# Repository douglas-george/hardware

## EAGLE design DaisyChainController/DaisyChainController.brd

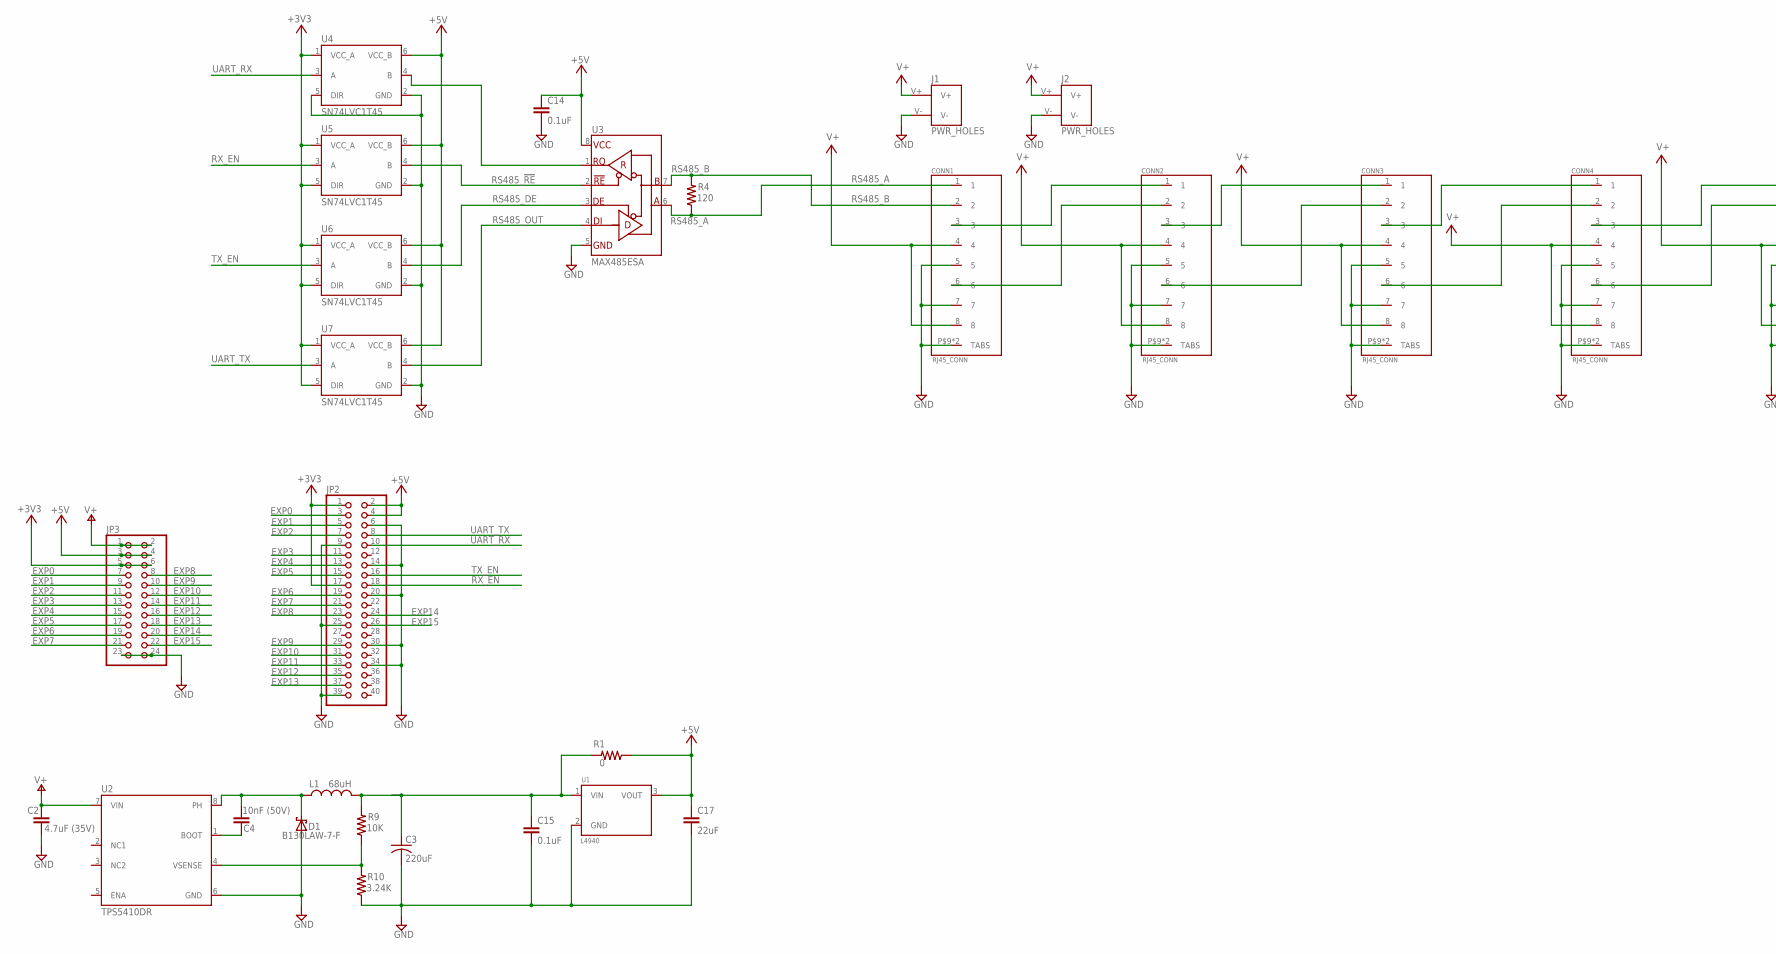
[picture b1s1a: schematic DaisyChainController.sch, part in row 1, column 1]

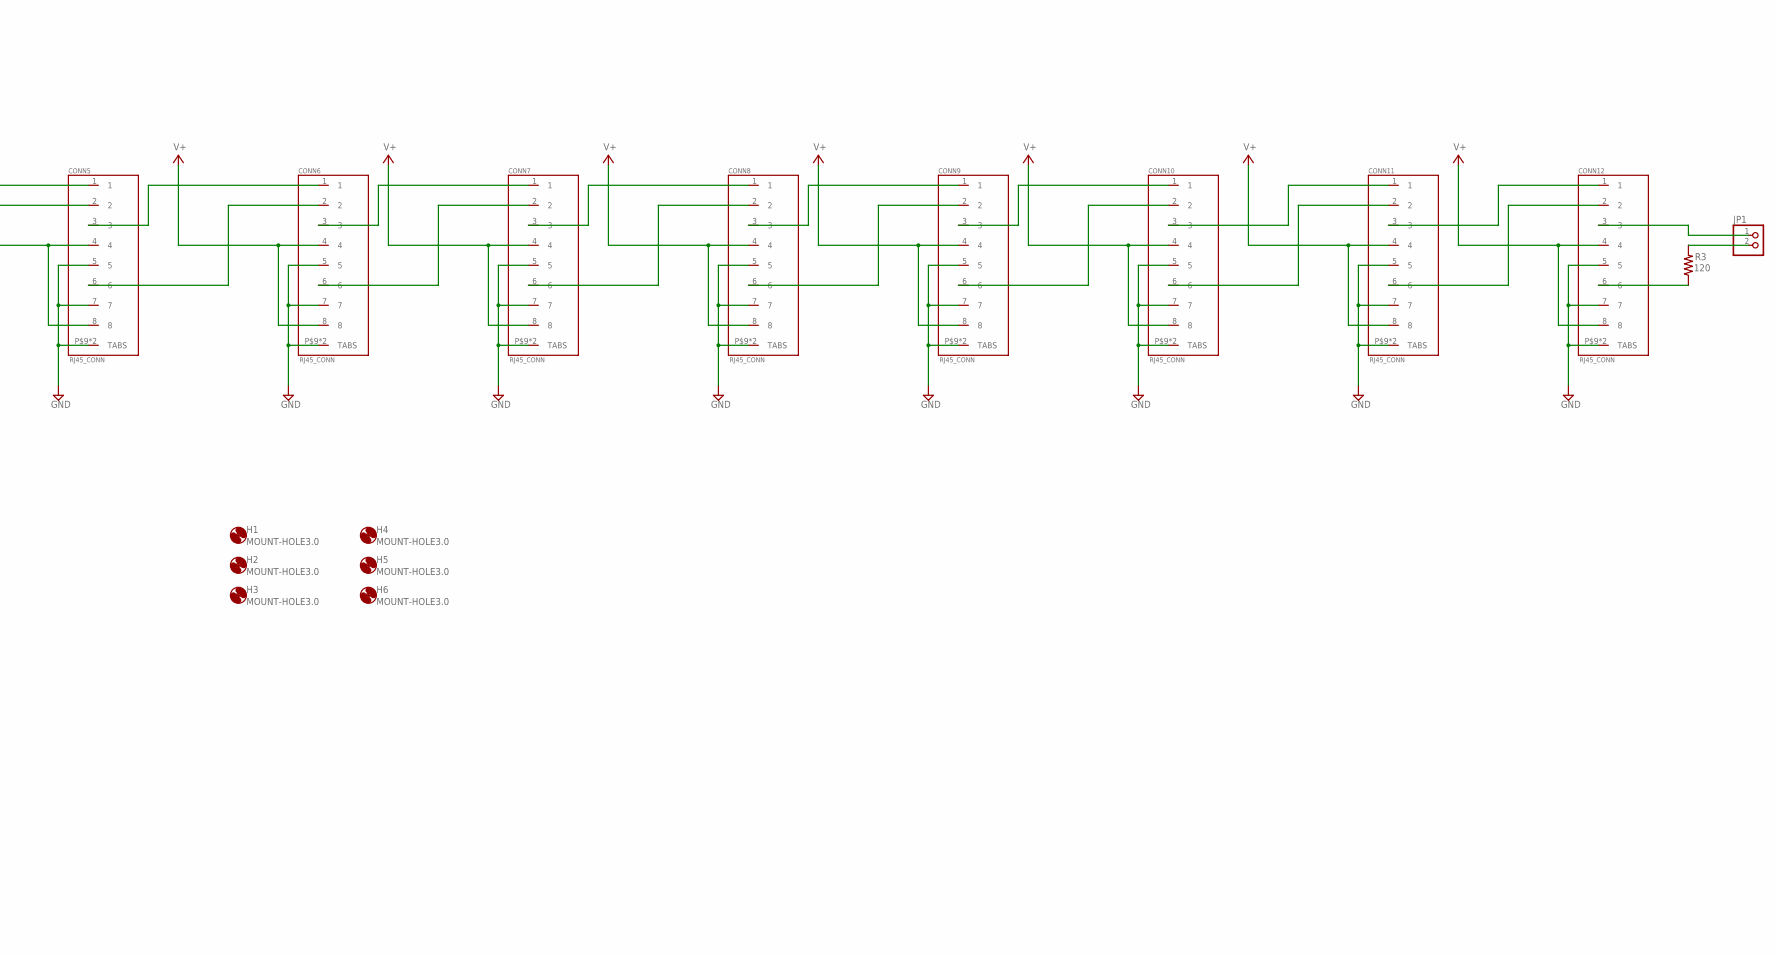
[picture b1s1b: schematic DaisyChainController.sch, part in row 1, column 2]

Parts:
C2: 4.7uF (35V); C0805
C3: 220uF; KEMET_D_CAP
C4: 10nF (50V); C0805
C14, C15: 0.1uF; C0805
C17: 22uF; C0805
CONN1, CONN2, CONN3, CONN4, CONN5, CONN6, CONN7, CONN8, CONN9, CONN10, CONN11, CONN12: RJ45_CONN; RJ45_VERT
D1: B130LAW-7-F; SOD123
H1, H2, H3, H4, H5, H6: MOUNT-HOLE3.0; 3,0
J1, J2: PWR_HOLES
JP1: PINHD-1X2; 1X02
JP2: PINHD-2X20/90; 2X20/90
JP3: PINHD-2X12; 2X12
L1: 68uH; CDRH127R
R1: 0; R0805
R3, R4: 120; R0805
R9: 10K; R0805
R10: 3.24K; R0805
U1: L4940; TO220
U2: TPS5410DR; SO08
U3: MAX485ESA; SO08
U4, U5, U6, U7: SN74LVC1T45; SOT23-6

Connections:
+3V3: JP2.1, JP2.17, JP3.5, JP3.6, U4.1 (VCC_A), U5.1 (VCC_A), U5.5 (DIR), U6.1 (VCC_A), U6.5 (DIR), U7.1 (VCC_A), U7.5 (DIR)
+5V: C14.1, C17.1, JP2.2, JP2.4, JP3.3, JP3.4, R1.1, U1.3 (VOUT), U3.8 (VCC), U4.6 (VCC_B), U5.6 (VCC_B), U6.6 (VCC_B), U7.6 (VCC_B)
EXP0: JP2.3, JP3.7
EXP1: JP2.5, JP3.9
EXP2: JP2.7, JP3.11
EXP3: JP2.11, JP3.13
EXP4: JP2.13, JP3.15
EXP5: JP2.15, JP3.17
EXP6: JP2.19, JP3.19
EXP7: JP2.21, JP3.21
EXP8: JP2.23, JP3.8
EXP9: JP2.29, JP3.10
EXP10: JP2.31, JP3.12
EXP11: JP2.33, JP3.14
EXP12: JP2.35, JP3.16
EXP13: JP2.37, JP3.18
EXP14: JP2.24, JP3.20
EXP15: JP2.26, JP3.22
GND: C2.2, C3.- (2), C14.2, C15.2, C17.2, CONN1.5, CONN1.7, CONN1.P$9 (TABS), CONN1.P$10 (TABS), CONN2.5, CONN2.7, CONN2.P$9 (TABS), CONN2.P$10 (TABS), CONN3.5, CONN3.7, CONN3.P$9 (TABS), CONN3.P$10 (TABS), CONN4.5, CONN4.7, CONN4.P$9 (TABS), CONN4.P$10 (TABS), CONN5.5, CONN5.7, CONN5.P$9 (TABS), CONN5.P$10 (TABS), CONN6.5, CONN6.7, CONN6.P$9 (TABS), CONN6.P$10 (TABS), CONN7.5, CONN7.7, CONN7.P$9 (TABS), CONN7.P$10 (TABS), CONN8.5, CONN8.7, CONN8.P$9 (TABS), CONN8.P$10 (TABS), CONN9.5, CONN9.7, CONN9.P$9 (TABS), CONN9.P$10 (TABS), CONN10.5, CONN10.7, CONN10.P$9 (TABS), CONN10.P$10 (TABS), CONN11.5, CONN11.7, CONN11.P$9 (TABS), CONN11.P$10 (TABS), CONN12.5, CONN12.7, CONN12.P$9 (TABS), CONN12.P$10 (TABS), D1.A, J1.V-, J2.V-, JP2.6, JP2.9, JP2.14, JP2.20, JP2.25, JP2.30, JP2.34, JP2.39, JP3.23, JP3.24, R10.1, U1.2 (GND), U2.6 (GND), U3.5 (GND), U4.2 (GND), U4.5 (DIR), U5.2 (GND), U6.2 (GND), U7.2 (GND)
unnamed: CONN1.6, CONN2.2
unnamed: C3.+ (1), C15.1, L1.P$2 (2), R1.2, R9.2, U1.1 (VIN)
unnamed: CONN1.3, CONN2.1
unnamed: CONN2.6, CONN3.2
unnamed: CONN3.6, CONN4.2
unnamed: CONN4.6, CONN5.2
unnamed: CONN5.6, CONN6.2
unnamed: CONN6.6, CONN7.2
unnamed: CONN7.6, CONN8.2
unnamed: CONN8.6, CONN9.2
unnamed: CONN9.6, CONN10.2
unnamed: CONN10.6, CONN11.2
unnamed: CONN11.6, CONN12.2
unnamed: CONN11.3, CONN12.1
unnamed: CONN10.3, CONN11.1
unnamed: U3.1 (RO), U4.4 (B)
unnamed: CONN8.3, CONN9.1
unnamed: CONN9.3, CONN10.1
unnamed: CONN7.3, CONN8.1
unnamed: CONN6.3, CONN7.1
unnamed: R9.1, R10.2, U2.4 (VSENSE)
unnamed: C4.1, D1.C, L1.1, U2.8 (PH)
unnamed: C4.2, U2.1 (BOOT)
unnamed: CONN5.3, CONN6.1
unnamed: CONN3.3, CONN4.1
unnamed: CONN2.3, CONN3.1
unnamed: CONN12.3, JP1.1
unnamed: CONN12.6, R3.1
unnamed: JP1.2, R3.2
unnamed: CONN4.3, CONN5.1
RS485_!RE: U3.2 (!RE), U5.4 (B)
RS485_A: CONN1.1, R4.1, U3.6 (A)
RS485_B: CONN1.2, R4.2, U3.7 (B)
RS485_DE: U3.3 (DE), U6.4 (B)
RS485_OUT: U3.4 (DI), U7.4 (B)
RX_EN: JP2.18, U5.3 (A)
TX_EN: JP2.16, U6.3 (A)
UART_RX: JP2.10, U4.3 (A)
UART_TX: JP2.8, U7.3 (A)
V+: C2.1, CONN1.4, CONN1.8, CONN2.4, CONN2.8, CONN3.4, CONN3.8, CONN4.4, CONN4.8, CONN5.4, CONN5.8, CONN6.4, CONN6.8, CONN7.4, CONN7.8, CONN8.4, CONN8.8, CONN9.4, CONN9.8, CONN10.4, CONN10.8, CONN11.4, CONN11.8, CONN12.4, CONN12.8, J1.V+, J2.V+, JP3.1, JP3.2, U2.7 (VIN)

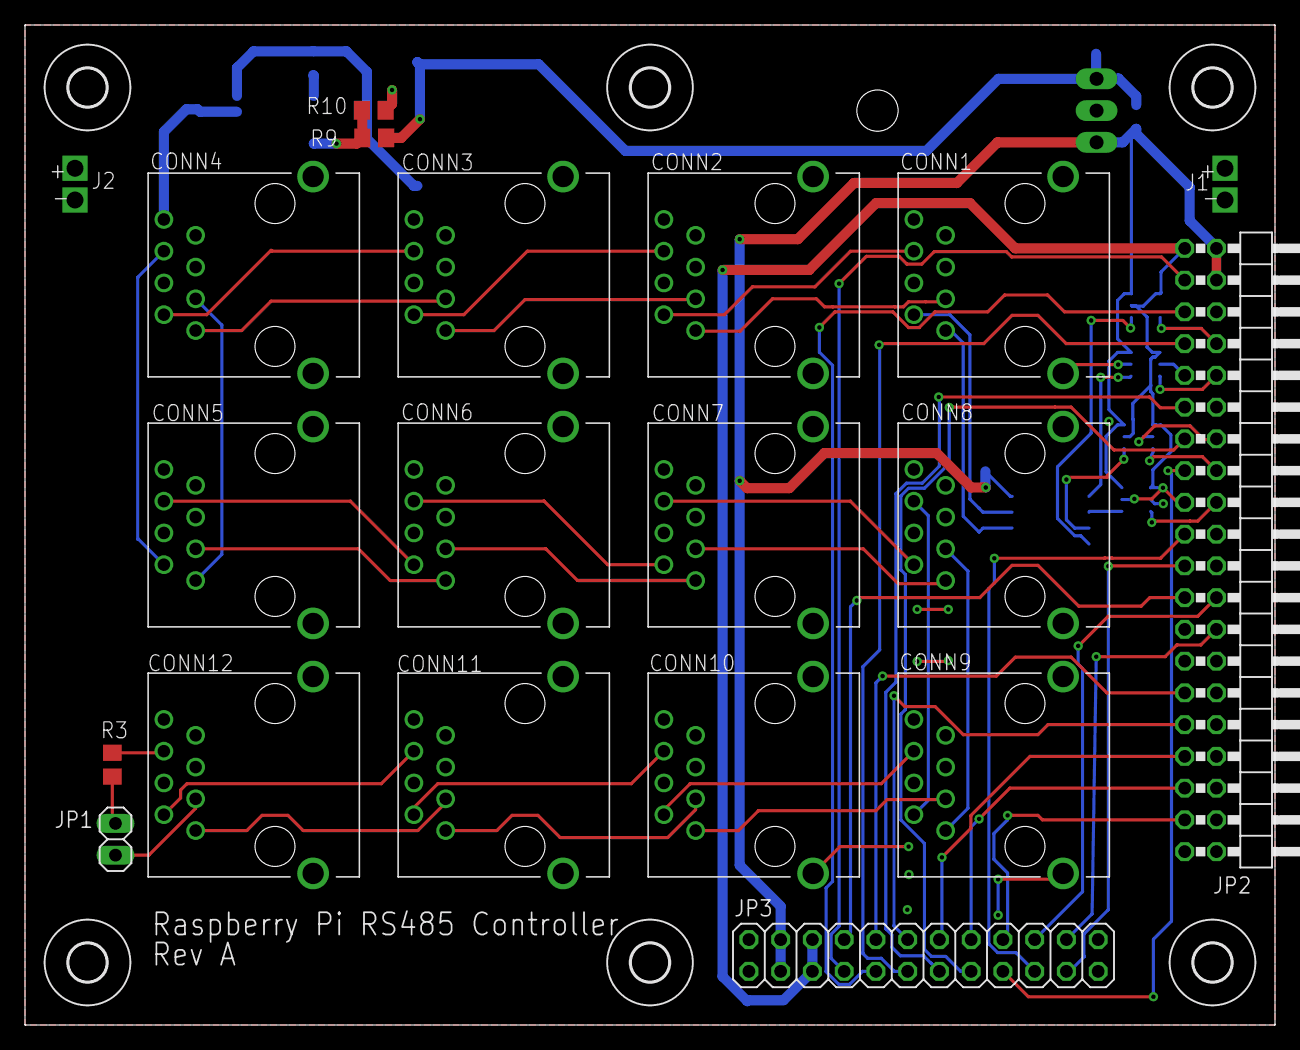
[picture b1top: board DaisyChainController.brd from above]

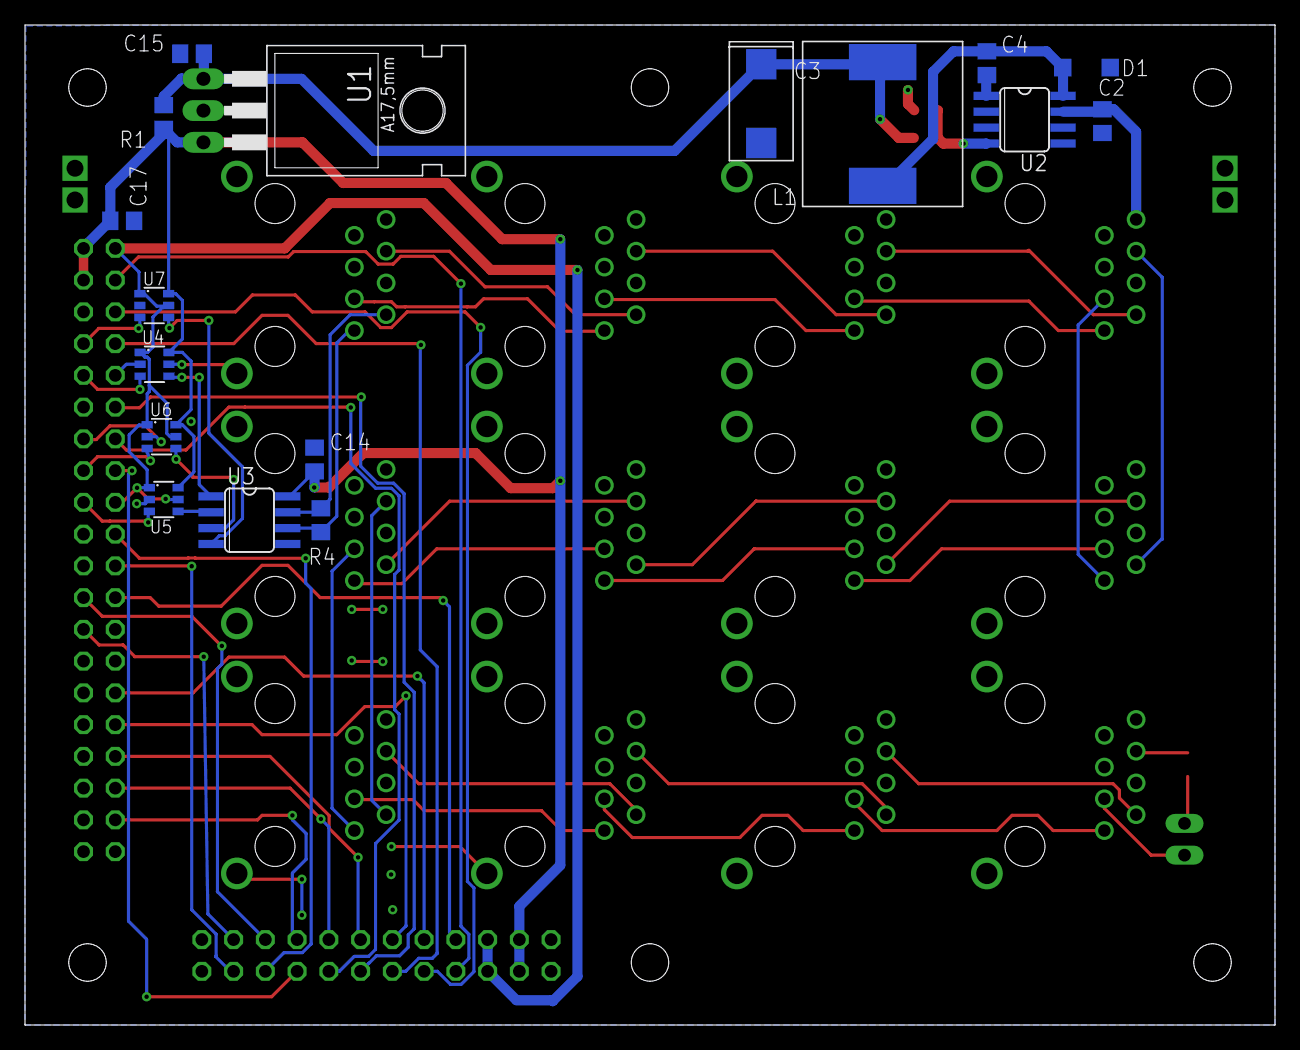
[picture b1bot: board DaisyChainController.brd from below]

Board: 2 copper layers, 100.0 x 80.0 mm, 43 parts (17 on the bottom side), 59 nets.

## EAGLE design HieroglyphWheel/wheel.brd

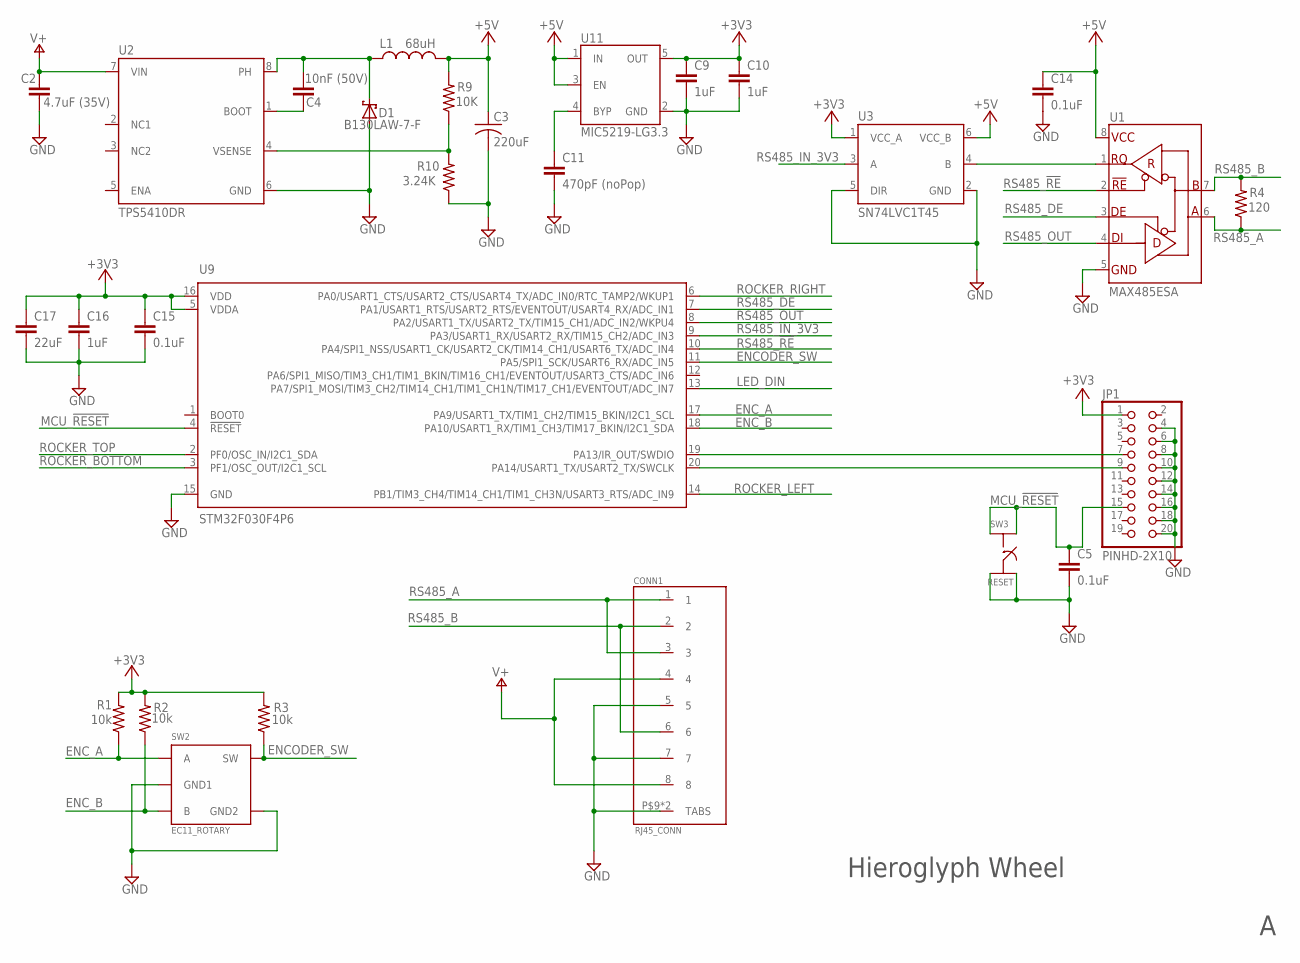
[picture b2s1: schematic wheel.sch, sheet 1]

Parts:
C2: 4.7uF (35V); C0805
C3: 220uF; KEMET_D_CAP
C4: 10nF (50V); C0805
C5, C14, C15: 0.1uF; C0805
C9, C10, C16: 1uF; C0805
C11: 470pF (noPop); C0805
C17: 22uF; C0805
CONN1: RJ45_CONN; RJ45_VERT
D1: B130LAW-7-F; SOD123
JP1: PINHD-2X10; 2X10_W_KEY
L1: 68uH; CDRH127R
R1, R2, R3: 10k; R0805
R4: 120; R0805
R9: 10K; R0805
R10: 3.24K; R0805
SW2: EC11_ROTARY
SW3: RESET; MOM_SWITCH
U1: MAX485ESA; SO08
U2: TPS5410DR; SO08
U3: SN74LVC1T45; SOT23-6
U9: STM32F030F4P6; TSSOP20
U11: MIC5219-LG3.3; SOT23-5

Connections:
+3V3: C9.1, C10.1, C15.1, C16.1, C17.1, JP1.1, R1.2, R2.2, R3.2, U3.1 (VCC_A), U9.5 (VDDA), U9.16 (VDD), U11.5 (OUT); also elsewhere on the board
+5V: C3.+ (1), C14.1, L1.P$2 (2), R9.2, U1.8 (VCC), U3.6 (VCC_B), U11.1 (IN), U11.3 (EN); also elsewhere on the board
ENCODER_SW: R3.1, SW2.SW, U9.11 (PA5/SPI1_SCK/USART6_RX/ADC_IN5)
ENC_A: R1.1, SW2.A, U9.17 (PA9/USART1_TX/TIM1_CH2/TIM15_BKIN/I2C1_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)
ENC_B: R2.1, SW2.B, U9.18 (PA10/USART1_RX/TIM1_CH3/TIM17_BKIN/I2C1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)
GND: C2.2, C3.- (2), C5.2, C9.2, C10.2, C11.2, C14.2, C15.2, C16.2, C17.2, CONN1.5, CONN1.7, CONN1.P$9 (TABS), CONN1.P$10 (TABS), D1.A, JP1.4, JP1.6, JP1.8, JP1.10, JP1.12, JP1.14, JP1.16, JP1.18, JP1.20, R10.1, SW2.C (GND1), SW2.D (GND2), SW3.P$3 (3), SW3.P$4 (4), U1.5 (GND), U2.6 (GND), U3.2 (GND), U3.5 (DIR), U9.15 (GND), U11.2 (GND); also elsewhere on the board
LED_DIN: U9.13 (PA7/SPI1_MOSI/TIM3_CH2/TIM14_CH1/TIM1_C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); also elsewhere on the board
MCU_!RESET: C5.1, JP1.15, SW3.P$1 (1), SW3.P$2 (2), U9.4 (!RESET)
unnamed: C11.1, U11.4 (BYP)
unnamed: R9.1, R10.2, U2.4 (VSENSE)
unnamed: C4.1, D1.C, L1.1, U2.8 (PH)
unnamed: C4.2, U2.1 (BOOT)
unnamed: JP1.7, U9.19 (PA13/IR_OUT/SWDIO)
unnamed: JP1.9, U9.20 (PA14/USART1_TX/USART2_TX/SWCLK)
unnamed: U1.1 (RO), U3.4 (B)
ROCKER_BOTTOM: U9.3 (PF1/OSC_OUT/I2C1_SCL); also elsewhere on the board
ROCKER_LEFT: U9.14 (PB1/TIM3_CH4/TIM14_CH1/TIM1_CH3N/USART3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); also elsewhere on the board
ROCKER_RIGHT: U9.6 (PA0/USART1_CTS/USART2_CTS/USART4_TX/ADC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); also elsewhere on the board
ROCKER_TOP: U9.2 (PF0/OSC_IN/I2C1_SDA); also elsewhere on the board
RS485_!RE: U1.2 (!RE), U9.10 (PA4/SPI1_NSS/USART1_CK/USART2_CK/TIM14_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)
RS485_A: CONN1.1, CONN1.3, R4.1, U1.6 (A)
RS485_B: CONN1.2, CONN1.6, R4.2, U1.7 (B)
RS485_DE: U1.3 (DE), U9.7 (PA1/USART1_RTS/USART2_RTS/EVENTOUT/USAR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)
RS485_IN_3V3: U3.3 (A), U9.9 (PA3/USART1_RX/USART2_RX/TIM15_CH2/ADC_I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)
RS485_OUT: U1.4 (DI), U9.8 (PA2/USART1_TX/USART2_TX/TIM15_CH1/ADC_I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)
V+: C2.1, CONN1.4, CONN1.8, U2.7 (VIN)

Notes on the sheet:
Hieroglyph Wheel

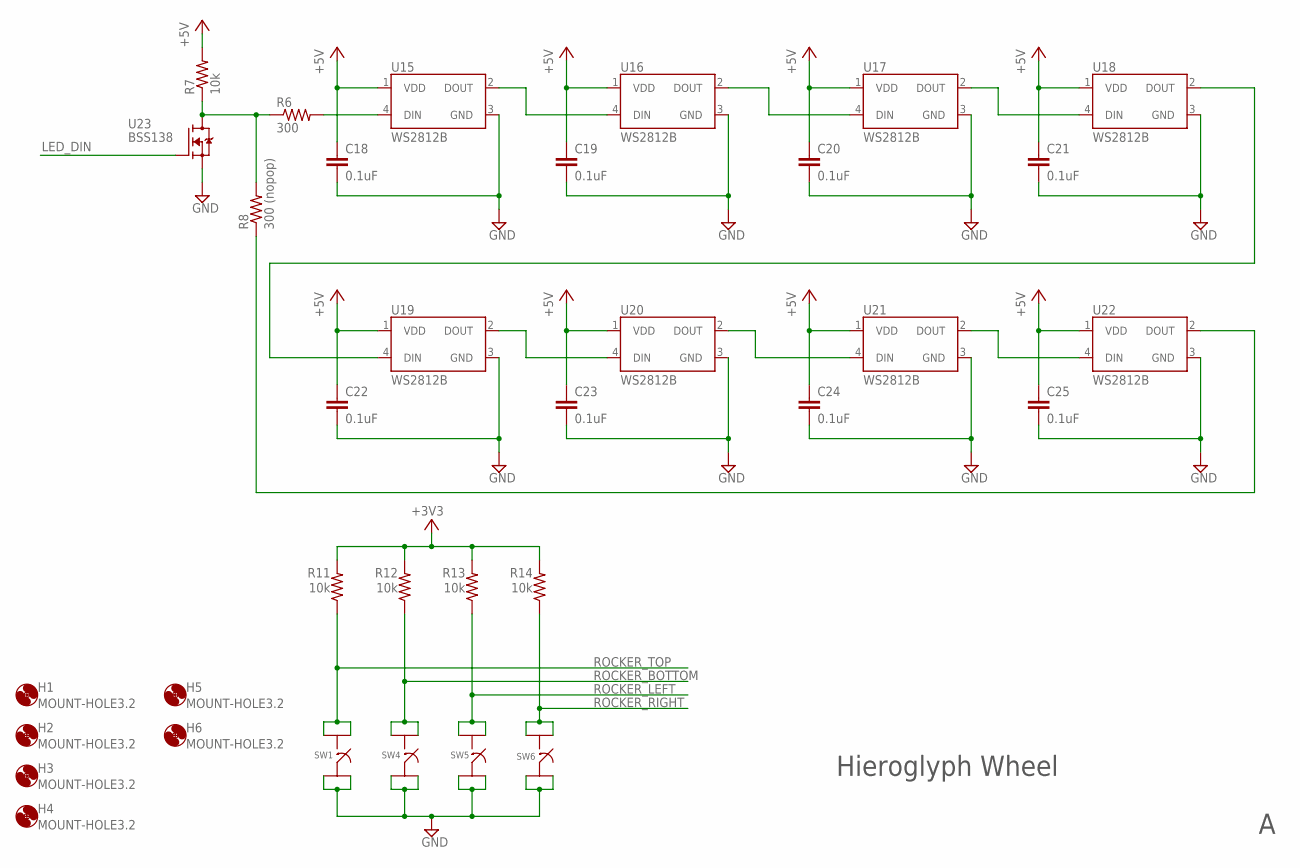
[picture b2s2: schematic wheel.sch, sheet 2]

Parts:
C18, C19, C20, C21, C22, C23, C24, C25: 0.1uF; C0805
H1, H2, H3, H4, H5, H6: MOUNT-HOLE3.2; 3,2
R6: 300; R0805
R7, R11, R12, R13, R14: 10k; R0805
R8: 300 (nopop); R0805
SW1, SW4, SW5, SW6: MOM_SWITCH
U15, U16, U17, U18, U19, U20, U21, U22: WS2812B
U23: BSS138; SOT23

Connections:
+3V3: R11.2, R12.2, R13.2, R14.2; also elsewhere on the board
+5V: C18.1, C19.1, C20.1, C21.1, C22.1, C23.1, C24.1, C25.1, R7.2, U15.1 (VDD), U16.1 (VDD), U17.1 (VDD), U18.1 (VDD), U19.1 (VDD), U20.1 (VDD), U21.1 (VDD), U22.1 (VDD); also elsewhere on the board
GND: C18.2, C19.2, C20.2, C21.2, C22.2, C23.2, C24.2, C25.2, SW1.P$3 (3), SW1.P$4 (4), SW4.P$3 (3), SW4.P$4 (4), SW5.P$3 (3), SW5.P$4 (4), SW6.P$3 (3), SW6.P$4 (4), U15.3 (GND), U16.3 (GND), U17.3 (GND), U18.3 (GND), U19.3 (GND), U20.3 (GND), U21.3 (GND), U22.3 (GND), U23.2 (S); also elsewhere on the board
LED_DIN: U23.1 (G); also elsewhere on the board
unnamed: U15.2 (DOUT), U16.4 (DIN)
unnamed: U16.2 (DOUT), U17.4 (DIN)
unnamed: U17.2 (DOUT), U18.4 (DIN)
unnamed: U19.2 (DOUT), U20.4 (DIN)
unnamed: U20.2 (DOUT), U21.4 (DIN)
unnamed: U21.2 (DOUT), U22.4 (DIN)
unnamed: U18.2 (DOUT), U19.4 (DIN)
unnamed: R6.2, U15.4 (DIN)
unnamed: R6.1, R7.1, R8.2, U23.3 (D)
unnamed: R8.1, U22.2 (DOUT)
ROCKER_BOTTOM: R12.1, SW4.P$1 (1), SW4.P$2 (2); also elsewhere on the board
ROCKER_LEFT: R13.1, SW5.P$1 (1), SW5.P$2 (2); also elsewhere on the board
ROCKER_RIGHT: R14.1, SW6.P$1 (1), SW6.P$2 (2); also elsewhere on the board
ROCKER_TOP: R11.1, SW1.P$1 (1), SW1.P$2 (2); also elsewhere on the board

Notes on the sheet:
Hieroglyph Wheel

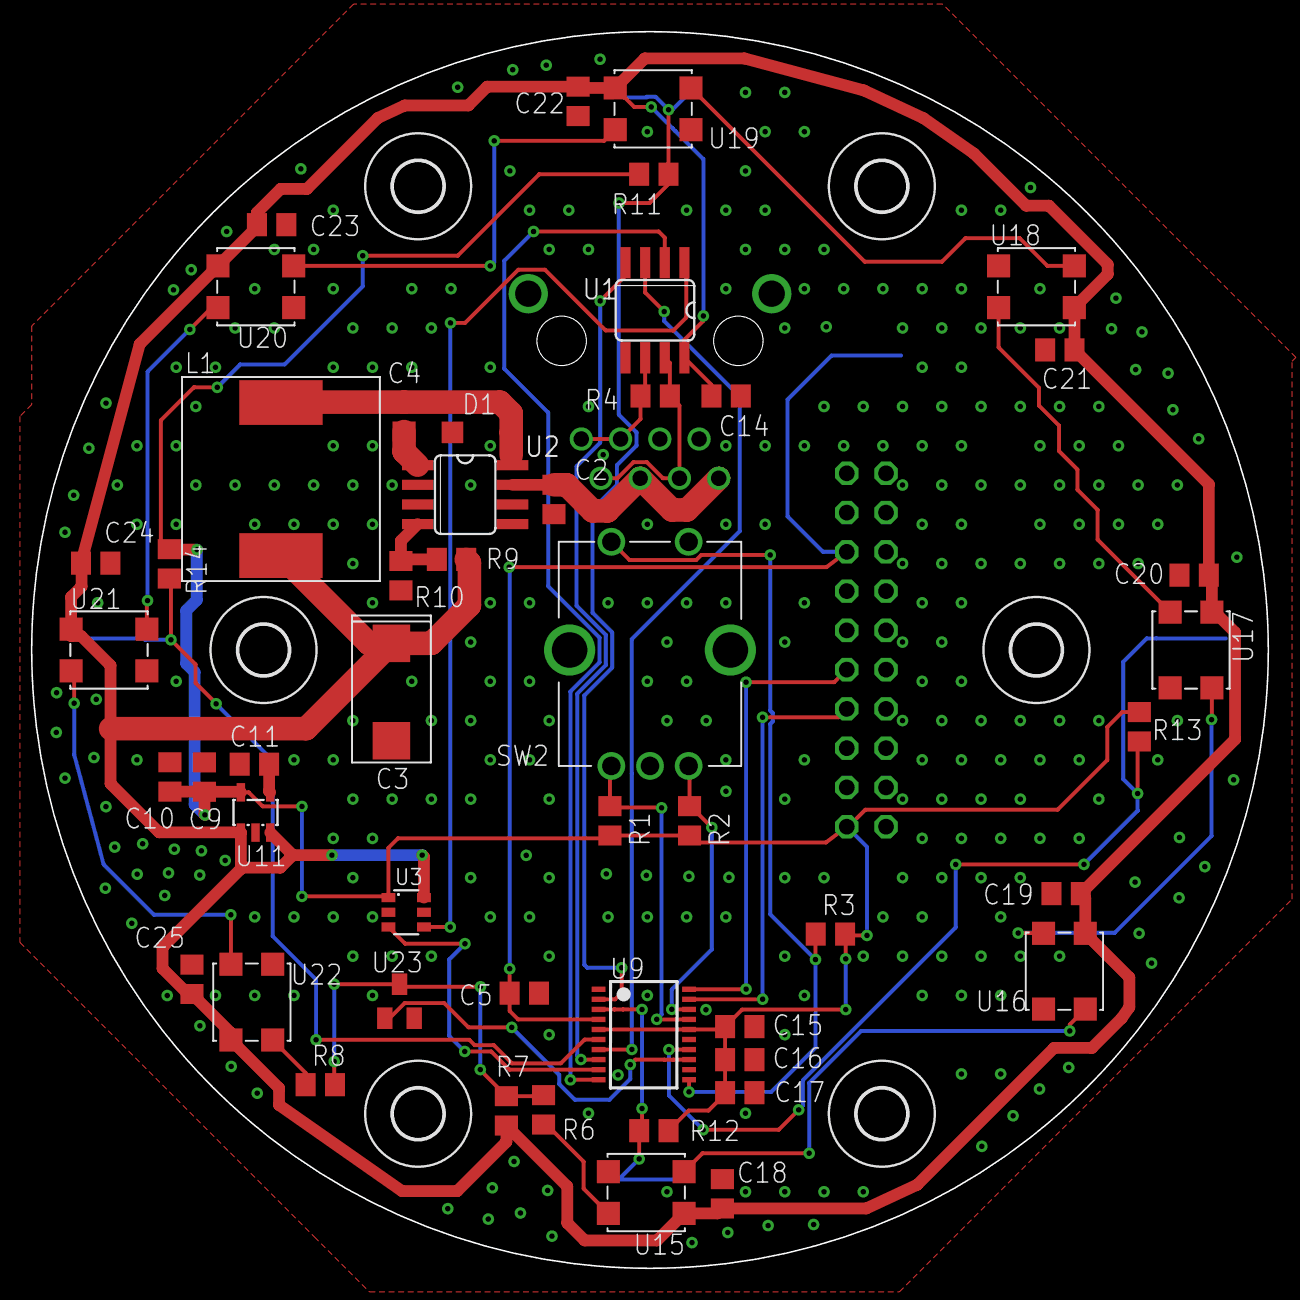
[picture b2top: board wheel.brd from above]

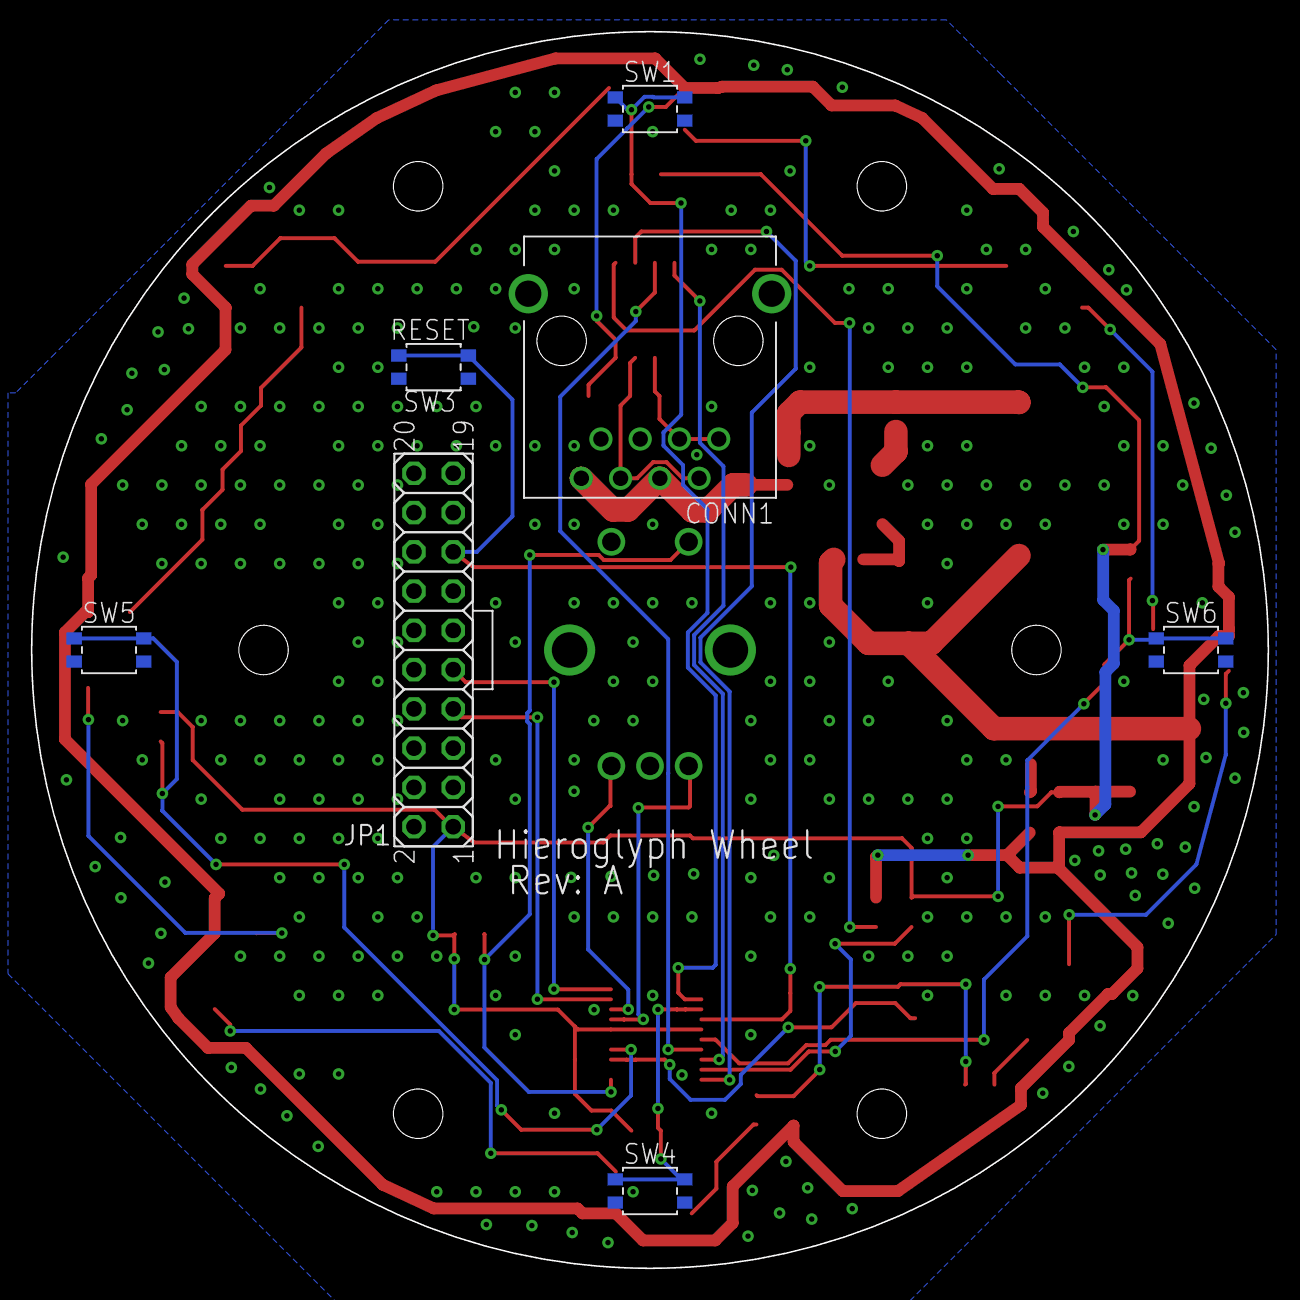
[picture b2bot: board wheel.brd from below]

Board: 2 copper layers, 80.0 x 80.0 mm, 62 parts (7 on the bottom side), 36 nets.

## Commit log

2018-12-30 Adding existing Eagle Files
